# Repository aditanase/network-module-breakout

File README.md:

network-module-breakout
=======================

Breakout board that makes it easy to connect NRF24 and Ethernet 5100 modules to a breadboard and SPI.

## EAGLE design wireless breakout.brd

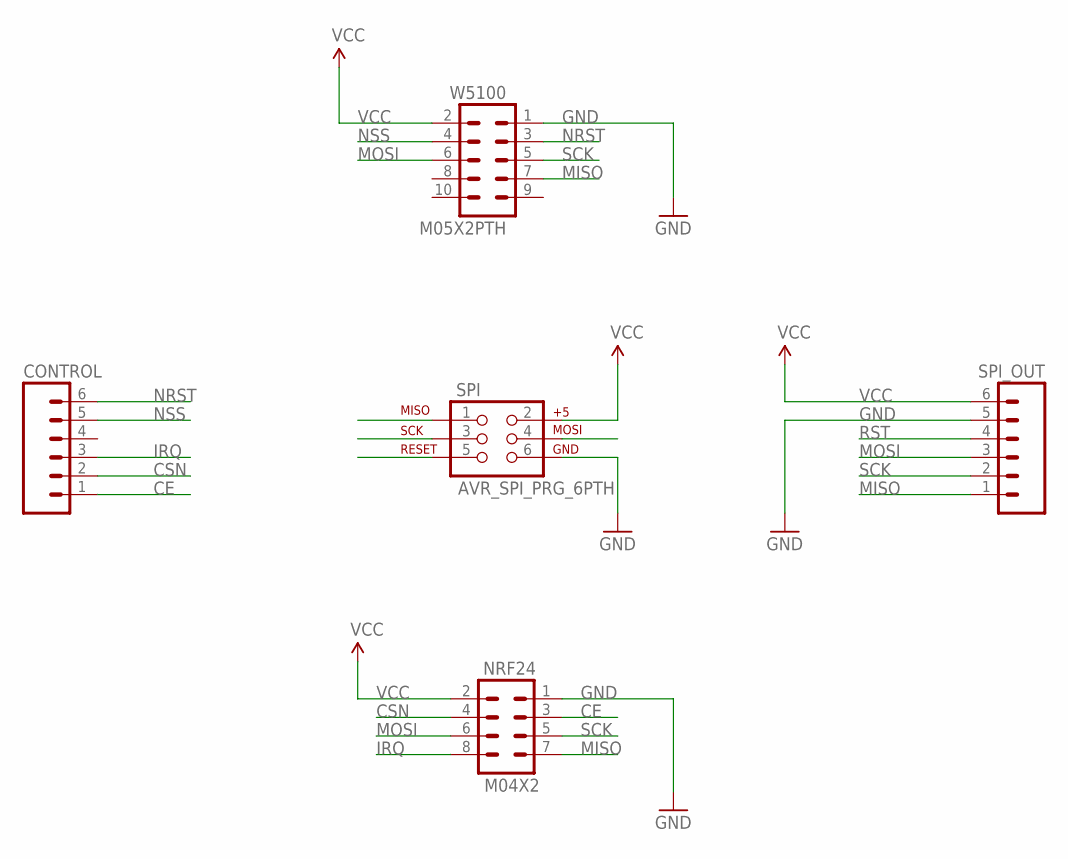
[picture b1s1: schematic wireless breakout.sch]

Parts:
CONTROL: M06LOCK; 1X06_LOCK
NRF24: M04X2; 2X4
SPI: AVR_SPI_PRG_6PTH; 2X3
SPI_OUT: M06LOCK; 1X06_LOCK
W5100: M05X2PTH; AVR_ICSP

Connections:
CE: CONTROL.1, NRF24.3
CSN: CONTROL.2, NRF24.4
GND: NRF24.1, SPI.6, SPI_OUT.5, W5100.1
IRQ: CONTROL.3, NRF24.8
MISO: NRF24.7, SPI.1, SPI_OUT.1, W5100.7
MOSI: NRF24.6, SPI.4, SPI_OUT.3, W5100.6
NRST: CONTROL.6, W5100.3
NSS: CONTROL.5, W5100.4
RST: SPI.5, SPI_OUT.4
SCK: NRF24.5, SPI.3, SPI_OUT.2, W5100.5
VCC: NRF24.2, SPI.2, SPI_OUT.6, W5100.2

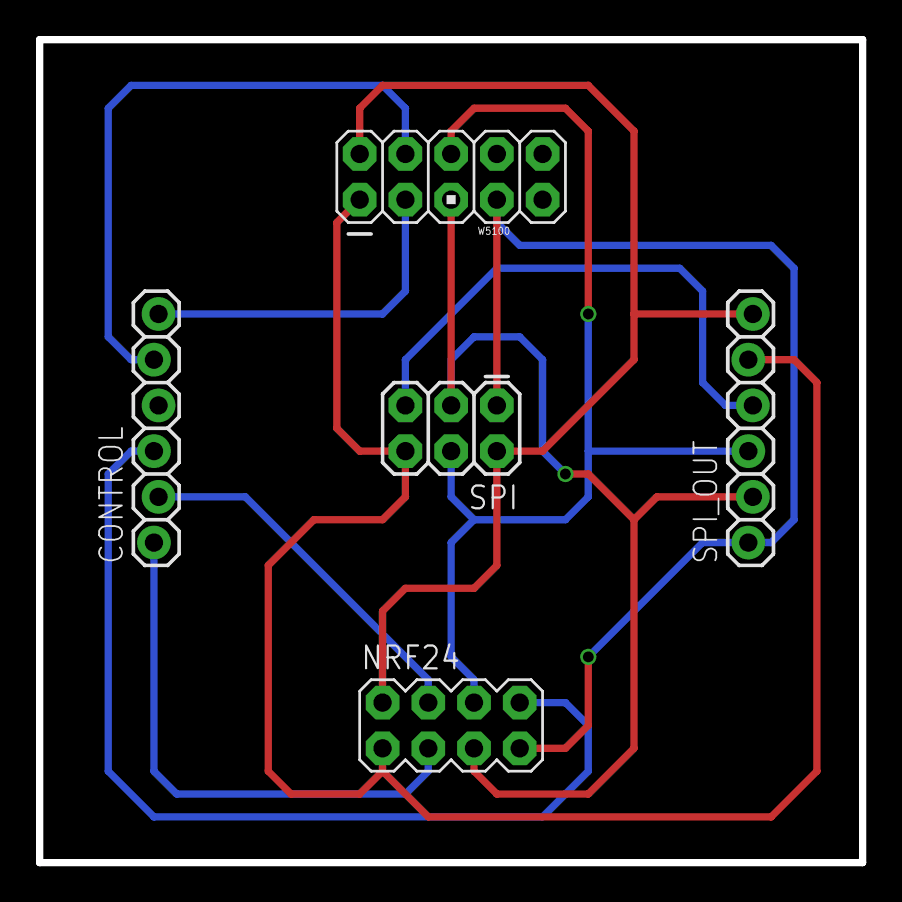
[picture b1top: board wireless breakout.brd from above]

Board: 2 copper layers, 45.7 x 45.7 mm, 5 parts (0 on the bottom side), 11 nets.

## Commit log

2014-05-22 Initial commit.
2014-05-22 Added top silk screen labels
2014-05-22 Flipped the nrf24 connector around.
2014-05-22 Updated with ITEAD rules

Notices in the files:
parts and their libraries:
SparkFun-Connectors: Licensing: Creative Commons ShareAlike 4.0 International - https://creativecommons.org/licenses/by-sa/4.0
